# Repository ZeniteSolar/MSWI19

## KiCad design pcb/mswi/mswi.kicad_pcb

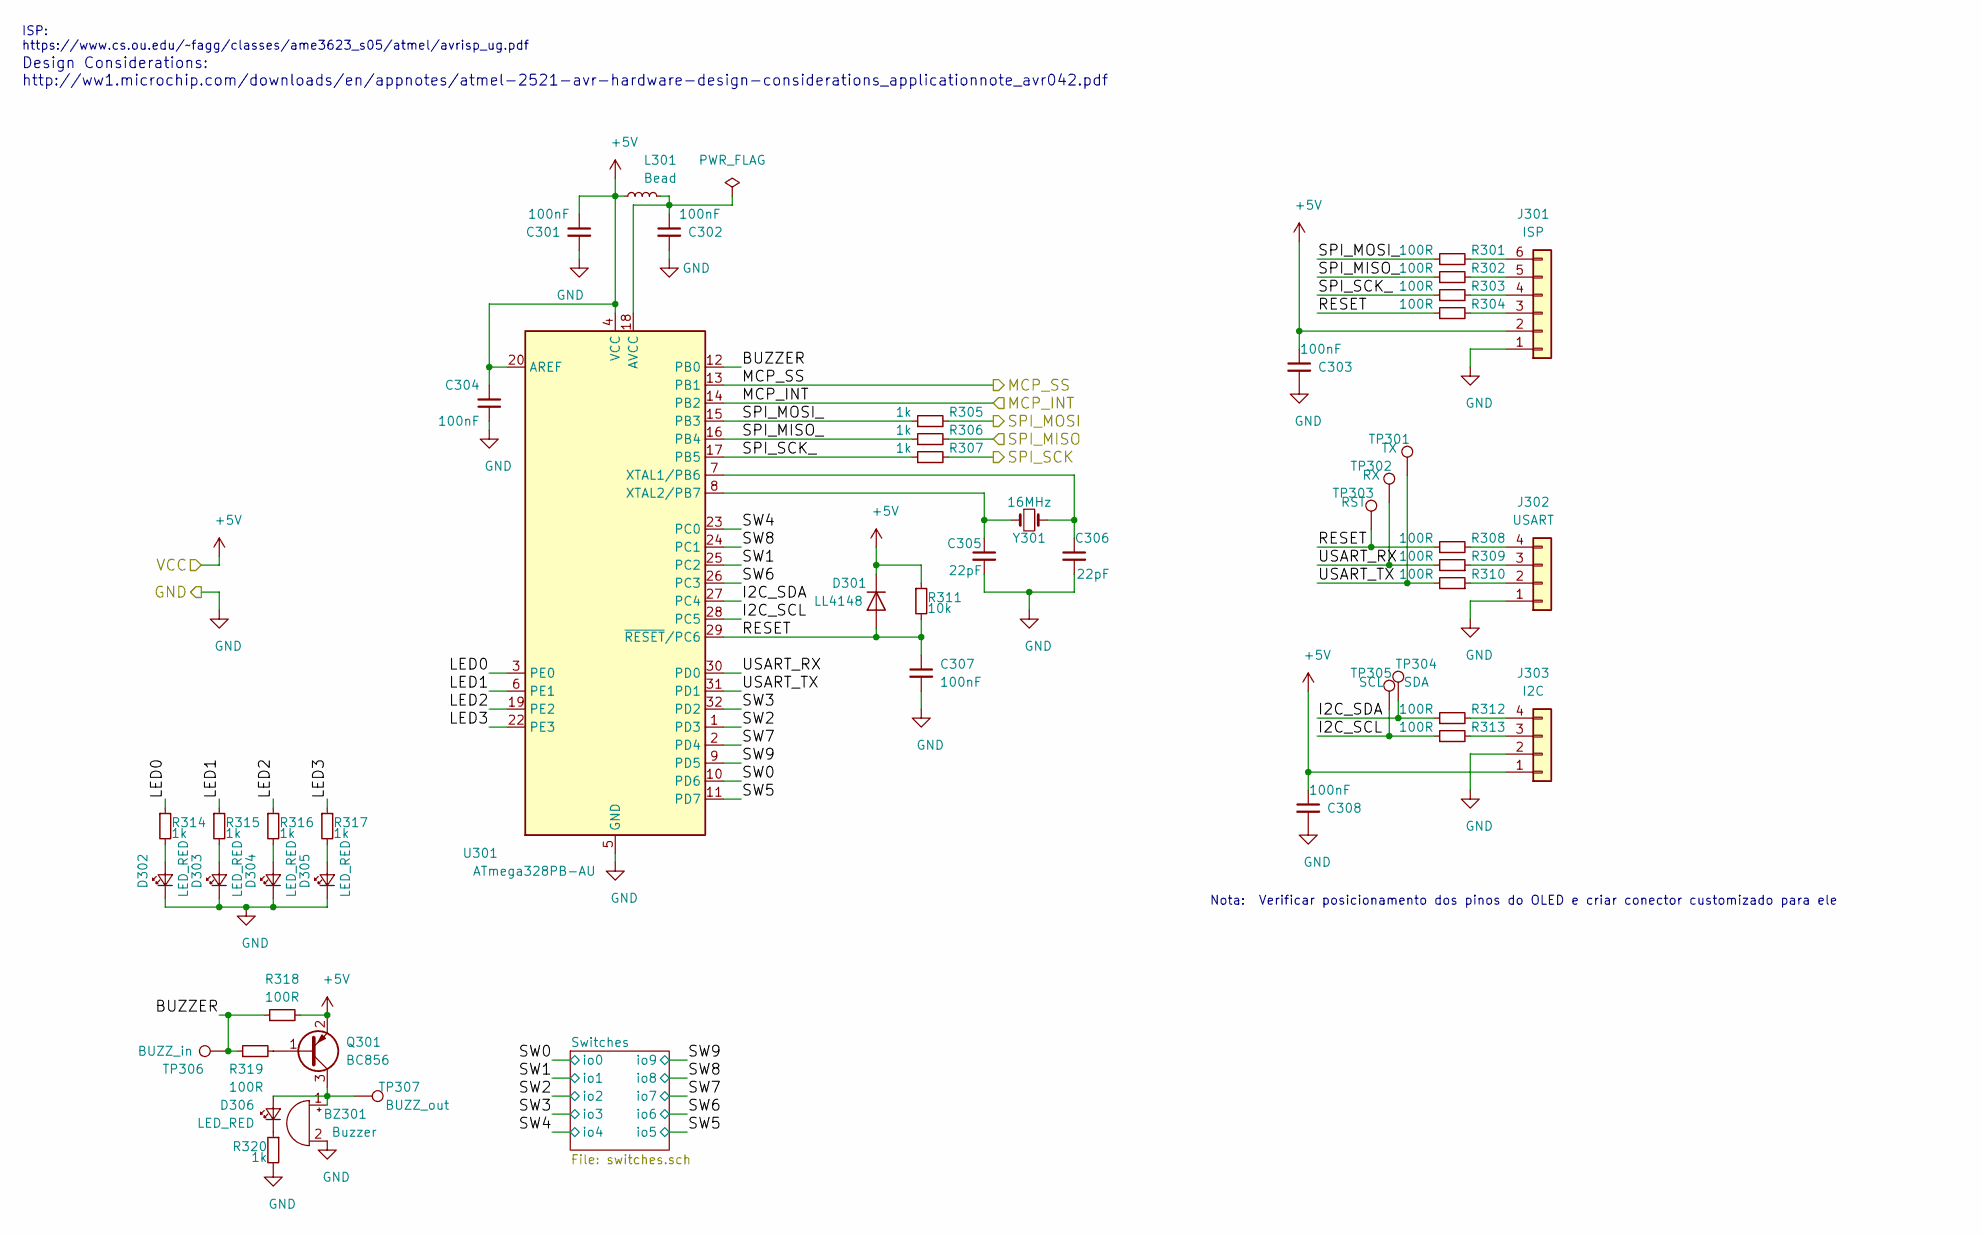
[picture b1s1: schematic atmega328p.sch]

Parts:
BZ301: Buzzer; Buzzer_12x9.5RM7.6
C301, C302, C303, C304, C307, C308: 100nF; C_0805_2012Metric_Pad1.15x1.40mm_HandSolder
C305, C306: 22pF; C_0805_2012Metric_Pad1.15x1.40mm_HandSolder
D301: LL4148; D_MiniMELF_Handsoldering
D302, D303, D304, D305, D306: LED_RED; LED_0805_2012Metric_Pad1.15x1.40mm_HandSolder
J301: ISP; PinHeader_1x06_P2.54mm_Vertical
J302: USART; PinHeader_1x04_P2.54mm_Vertical
J303: I2C; PinHeader_1x04_P2.54mm_Vertical
L301: Bead; L_0805_2012Metric_Pad1.15x1.40mm_HandSolder
Q301: BC856; SOT-23
R301, R302, R303, R304, R308, R309, R310, R312, R313, R318, R319: 100R; R_0805_2012Metric_Pad1.15x1.40mm_HandSolder
R305, R306, R307, R314, R315, R316, R317, R320: 1k; R_0805_2012Metric_Pad1.15x1.40mm_HandSolder
R311: 10k; R_0805_2012Metric_Pad1.15x1.40mm_HandSolder
TP301: TX; TestPoint_Pad_2.0x2.0mm
TP302: RX; TestPoint_Pad_2.0x2.0mm
TP303: RST; TestPoint_Pad_2.0x2.0mm
TP304: SDA; TestPoint_Pad_2.0x2.0mm
TP305: SCL; TestPoint_Pad_2.0x2.0mm
TP306: BUZZ_in; TestPoint_Pad_2.0x2.0mm
TP307: BUZZ_out; TestPoint_Pad_2.0x2.0mm
U301: ATmega328PB-AU; TQFP-32_7x7mm_P0.8mm
Y301: 16MHz; Crystal_HC49-U_Vertical

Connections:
+5V: C301.1, C303.1, C304.2, C308.1, D301.1 (K), J301.2, J303.1, L301.1, Q301.2 (E), R311.1, R318.2, U301.4 (VCC), U301.20 (AREF); also elsewhere on the board
/CANBUS/CS: U301.13 (PB1); also elsewhere on the board
/CANBUS/INT: U301.14 (PB2); also elsewhere on the board
/CANBUS/SCK: R307.2; also elsewhere on the board
/CANBUS/SI: R305.2; also elsewhere on the board
/CANBUS/SO: R306.2; also elsewhere on the board
/MCU/BUZZER: R318.1, R319.1, TP306.1, U301.12 (PB0)
/MCU/I2C_SCL: R313.1, TP305.1, U301.28 (PC5)
/MCU/I2C_SDA: R312.1, TP304.1, U301.27 (PC4)
/MCU/LED0: R314.1, U301.3 (PE0)
/MCU/LED1: R315.1, U301.6 (PE1)
/MCU/LED2: R316.1, U301.19 (PE2)
/MCU/LED3: R317.1, U301.22 (PE3)
/MCU/RESET: C307.1, D301.2 (A), R304.1, R308.1, R311.2, TP303.1, U301.29 (~RESET~/PC6)
/MCU/SPI_MISO_: R302.1, R306.1, U301.16 (PB4)
/MCU/SPI_MOSI_: R301.1, R305.1, U301.15 (PB3)
/MCU/SPI_SCK_: R303.1, R307.1, U301.17 (PB5)
/MCU/SW0: U301.10 (PD6); also elsewhere on the board
/MCU/SW1: U301.25 (PC2); also elsewhere on the board
/MCU/SW2: U301.1 (PD3); also elsewhere on the board
/MCU/SW3: U301.32 (PD2); also elsewhere on the board
/MCU/SW4: U301.23 (PC0); also elsewhere on the board
/MCU/SW5: U301.11 (PD7); also elsewhere on the board
/MCU/SW6: U301.26 (PC3); also elsewhere on the board
/MCU/SW7: U301.2 (PD4); also elsewhere on the board
/MCU/SW8: U301.24 (PC1); also elsewhere on the board
/MCU/SW9: U301.9 (PD5); also elsewhere on the board
/MCU/USART_RX: R309.2, TP302.1, U301.30 (PD0)
/MCU/USART_TX: R310.2, TP301.1, U301.31 (PD1)
GND: BZ301.2 (+), C301.2, C302.2, C303.2, C304.1, C305.2, C306.2, C307.2, C308.2, D302.1 (K), D303.1 (K), D304.1 (K), D305.1 (K), J301.1, J302.1, J303.2, R320.2, U301.5 (GND), U301.21 (GND); also elsewhere on the board
unnamed: BZ301.1 (-), D306.2 (A), Q301.3 (C), TP307.1
unnamed: C302.1, L301.2, U301.18 (AVCC)
unnamed: C305.1, U301.8 (XTAL2/PB7), Y301.1
unnamed: C306.1, U301.7 (XTAL1/PB6), Y301.2
unnamed: D302.2 (A), R314.2
unnamed: D303.2 (A), R315.2
unnamed: D304.2 (A), R316.2
unnamed: D305.2 (A), R317.2
unnamed: D306.1 (K), R320.1
unnamed: J301.3, R304.2
unnamed: J301.4, R303.2
unnamed: J301.5, R302.2
unnamed: J301.6, R301.2
unnamed: J302.2, R310.1
unnamed: J302.3, R309.1
unnamed: J302.4, R308.2
unnamed: J303.3, R313.2
unnamed: J303.4, R312.2
unnamed: Q301.1 (B), R319.2

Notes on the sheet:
Design Considerations: http://ww1.microchip.com/downloads/en/appnotes/atmel-2521-avr-hardware-design-considerations_applicationnote_avr042.pdf
ISP: https://www.cs.ou.edu/~~fagg/classes/ame3623_s05/atmel/avrisp_ug.pdf
Nota: Verificar posicionamento dos pinos do OLED e criar conector customizado para ele

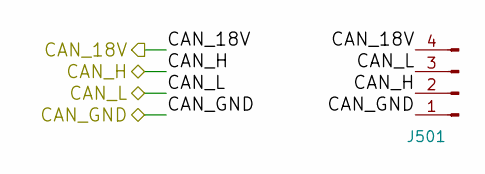
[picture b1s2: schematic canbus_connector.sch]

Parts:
J501: Conn_01x04_Male

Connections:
/CANBUS CONN/CAN_GND: J501.1; also elsewhere on the board
/CANBUS CONN/CAN_H: J501.2; also elsewhere on the board
/CANBUS CONN/CAN_L: J501.3; also elsewhere on the board
/POWER SUPPLY/+18V_IN: J501.4; also elsewhere on the board

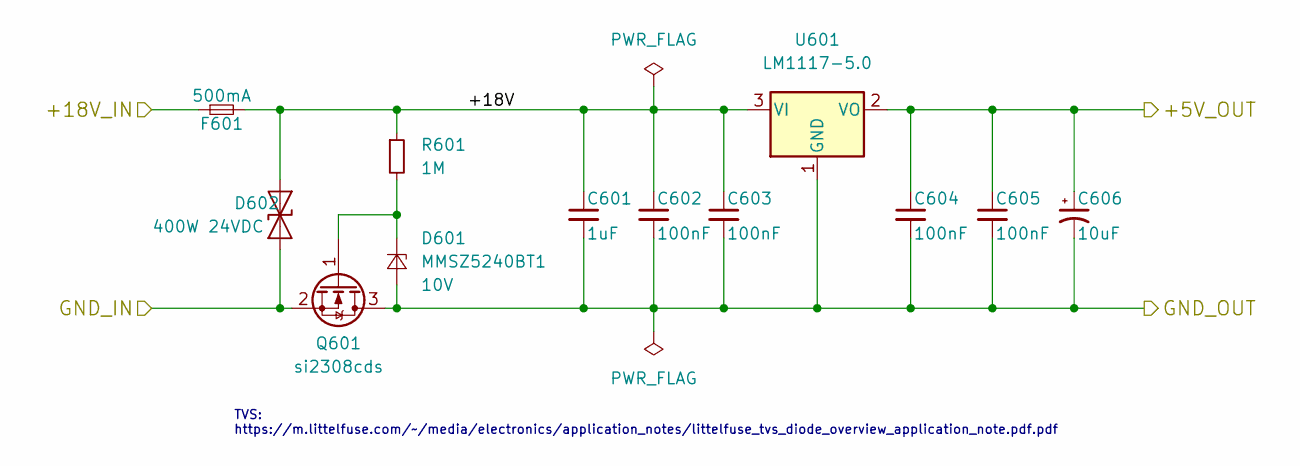
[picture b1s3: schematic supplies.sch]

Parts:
C601: 1uF; C_0805_2012Metric_Pad1.15x1.40mm_HandSolder
C602, C603, C604, C605: 100nF; C_0805_2012Metric_Pad1.15x1.40mm_HandSolder
C606: 10uF; CP_EIA-6032-20_AVX-F_Pad2.25x2.35mm_HandSolder
D601: MMSZ5240BT1; D_SOD-123; Voltage 10V
D602: 400W 24VDC; D_SMA
F601: 500mA; Fuse_1206_3216Metric_Pad1.42x1.75mm_HandSolder
Q601: si2308cds; SOT-23
R601: 1M; R_0805_2012Metric_Pad1.15x1.40mm_HandSolder
U601: LM1117-5.0; SOT-223-3_TabPin2

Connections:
+5V: C604.1, C605.1, C606.1, U601.2 (VO); also elsewhere on the board
/CANBUS CONN/CAN_GND: D602.2 (A2), Q601.2 (S); also elsewhere on the board
/POWER SUPPLY/+18V: C601.1, C602.1, C603.1, D602.1 (A1), F601.2, R601.1, U601.3 (VI)
/POWER SUPPLY/+18V_IN: F601.1; also elsewhere on the board
GND: C601.2, C602.2, C603.2, C604.2, C605.2, C606.2, D601.2 (A), Q601.3 (D), U601.1 (GND); also elsewhere on the board
unnamed: D601.1 (K), Q601.1 (G), R601.2

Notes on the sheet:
TVS: https://m.littelfuse.com/~~/media/electronics/application_notes/littelfuse_tvs_diode_overview_application_note.pdf.pdf

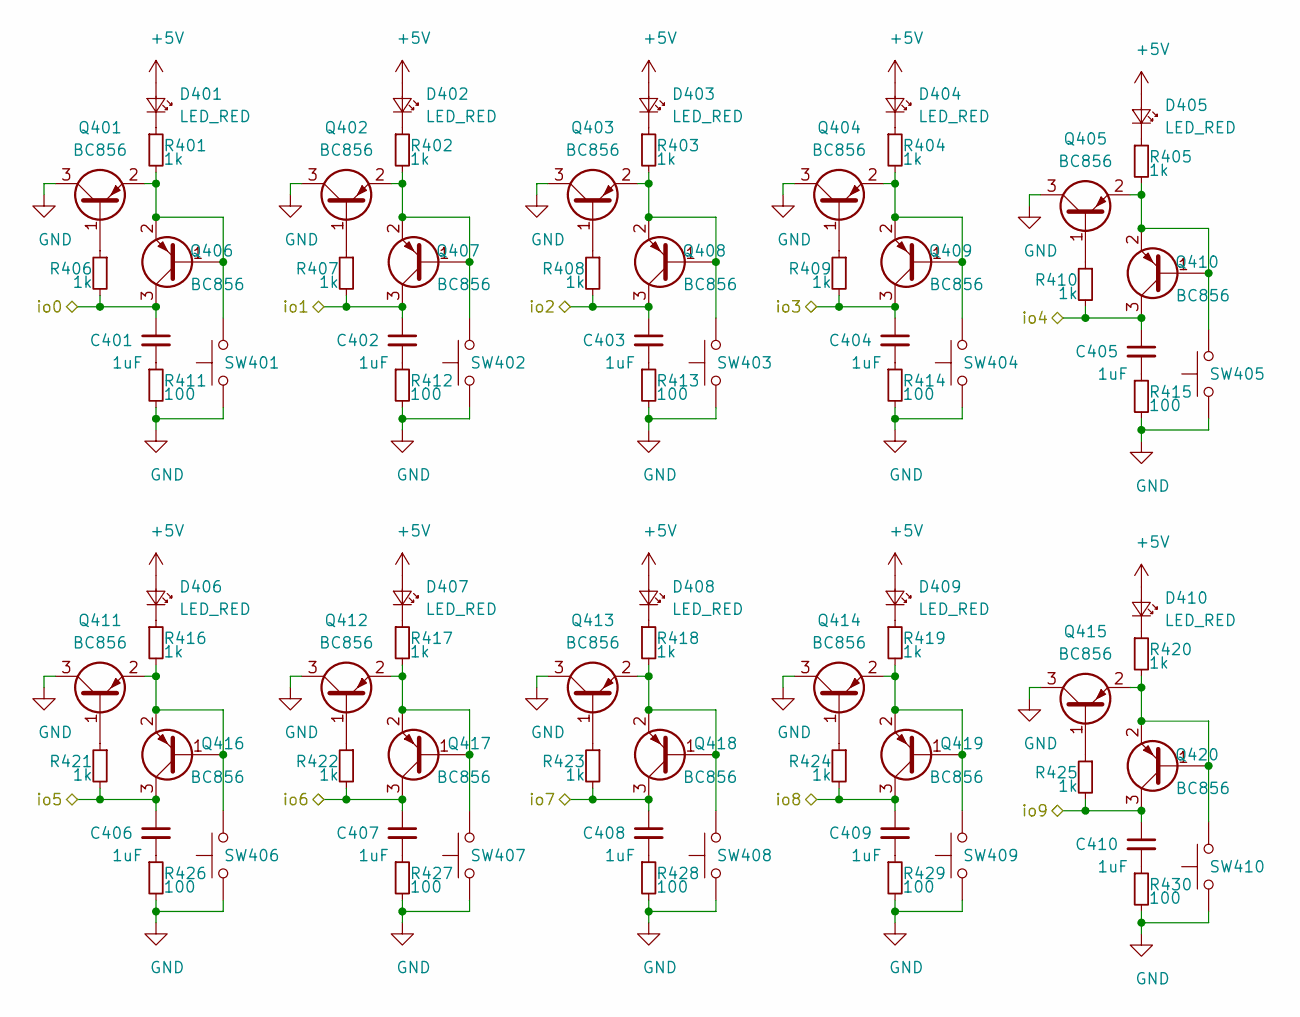
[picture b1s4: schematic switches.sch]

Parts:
C401, C402, C403, C404, C405, C406, C407, C408, C409, C410: 1uF; C_0805_2012Metric_Pad1.15x1.40mm_HandSolder
D401, D402, D403, D404, D405, D406, D407, D408, D409, D410: LED_RED; LED_0805_2012Metric_Pad1.15x1.40mm_HandSolder
Q401, Q402, Q403, Q404, Q405, Q406, Q407, Q408, Q409, Q410, Q411, Q412, Q413, Q414, Q415, Q416, Q417, Q418, Q419, Q420: BC856; SOT-23
R401, R402, R403, R404, R405, R406, R407, R408, R409, R410, R416, R417, R418, R419, R420, R421, R422, R423, R424, R425: 1k; R_0805_2012Metric_Pad1.15x1.40mm_HandSolder
R411, R412, R413, R414, R415, R426, R427, R428, R429, R430: 100; R_0805_2012Metric_Pad1.15x1.40mm_HandSolder
SW401, SW402, SW403, SW404, SW405, SW406, SW407, SW408, SW409, SW410: SW_Push; SW_PUSH-12mm

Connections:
+5V: D401.2 (A), D402.2 (A), D403.2 (A), D404.2 (A), D405.2 (A), D406.2 (A), D407.2 (A), D408.2 (A), D409.2 (A), D410.2 (A); also elsewhere on the board
/MCU/SW0: C401.1, Q406.3 (C), R406.2; also elsewhere on the board
/MCU/SW1: C402.1, Q407.3 (C), R407.2; also elsewhere on the board
/MCU/SW2: C403.1, Q408.3 (C), R408.2; also elsewhere on the board
/MCU/SW3: C404.1, Q409.3 (C), R409.2; also elsewhere on the board
/MCU/SW4: C405.1, Q410.3 (C), R410.2; also elsewhere on the board
/MCU/SW5: C406.1, Q416.3 (C), R421.2; also elsewhere on the board
/MCU/SW6: C407.1, Q417.3 (C), R422.2; also elsewhere on the board
/MCU/SW7: C408.1, Q418.3 (C), R423.2; also elsewhere on the board
/MCU/SW8: C409.1, Q419.3 (C), R424.2; also elsewhere on the board
/MCU/SW9: C410.1, Q420.3 (C), R425.2; also elsewhere on the board
GND: Q401.3 (C), Q402.3 (C), Q403.3 (C), Q404.3 (C), Q405.3 (C), Q411.3 (C), Q412.3 (C), Q413.3 (C), Q414.3 (C), Q415.3 (C), R411.2, R412.2, R413.2, R414.2, R415.2, R426.2, R427.2, R428.2, R429.2, R430.2, SW401.1, SW402.1, SW403.1, SW404.1, SW405.1, SW406.1, SW407.1, SW408.1, SW409.1, SW410.1; also elsewhere on the board
unnamed: C401.2, R411.1
unnamed: C402.2, R412.1
unnamed: C403.2, R413.1
unnamed: C404.2, R414.1
unnamed: C405.2, R415.1
unnamed: C406.2, R426.1
unnamed: C407.2, R427.1
unnamed: C408.2, R428.1
unnamed: C409.2, R429.1
unnamed: C410.2, R430.1
unnamed: D401.1 (K), R401.1
unnamed: D402.1 (K), R402.1
unnamed: D403.1 (K), R403.1
unnamed: D404.1 (K), R404.1
unnamed: D405.1 (K), R405.1
unnamed: D406.1 (K), R416.1
unnamed: D407.1 (K), R417.1
unnamed: D408.1 (K), R418.1
unnamed: D409.1 (K), R419.1
unnamed: D410.1 (K), R420.1
unnamed: Q401.1 (B), R406.1
unnamed: Q401.2 (E), Q406.1 (B), Q406.2 (E), R401.2, SW401.2
unnamed: Q402.1 (B), R407.1
unnamed: Q402.2 (E), Q407.1 (B), Q407.2 (E), R402.2, SW402.2
unnamed: Q403.1 (B), R408.1
unnamed: Q403.2 (E), Q408.1 (B), Q408.2 (E), R403.2, SW403.2
unnamed: Q404.1 (B), R409.1
unnamed: Q404.2 (E), Q409.1 (B), Q409.2 (E), R404.2, SW404.2
unnamed: Q405.1 (B), R410.1
unnamed: Q405.2 (E), Q410.1 (B), Q410.2 (E), R405.2, SW405.2
unnamed: Q411.1 (B), R421.1
unnamed: Q411.2 (E), Q416.1 (B), Q416.2 (E), R416.2, SW406.2
unnamed: Q412.1 (B), R422.1
unnamed: Q412.2 (E), Q417.1 (B), Q417.2 (E), R417.2, SW407.2
unnamed: Q413.1 (B), R423.1
unnamed: Q413.2 (E), Q418.1 (B), Q418.2 (E), R418.2, SW408.2
unnamed: Q414.1 (B), R424.1
unnamed: Q414.2 (E), Q419.1 (B), Q419.2 (E), R419.2, SW409.2
unnamed: Q415.1 (B), R425.1
unnamed: Q415.2 (E), Q420.1 (B), Q420.2 (E), R420.2, SW410.2

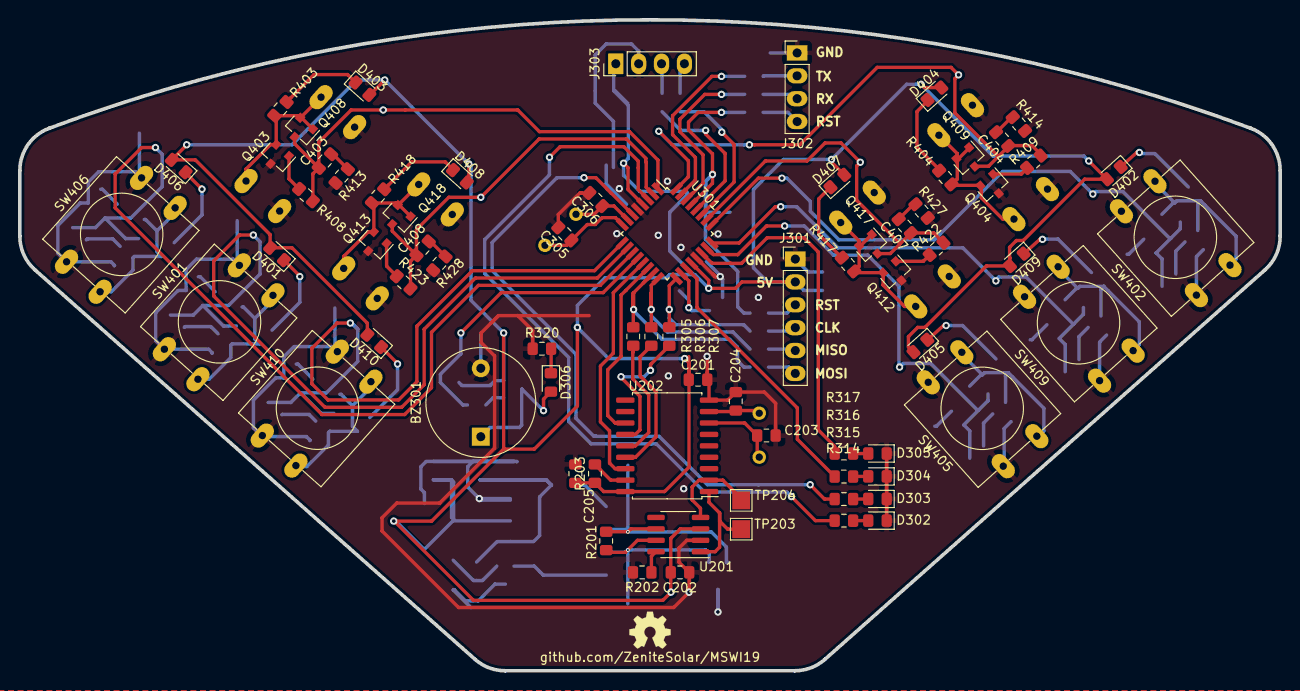
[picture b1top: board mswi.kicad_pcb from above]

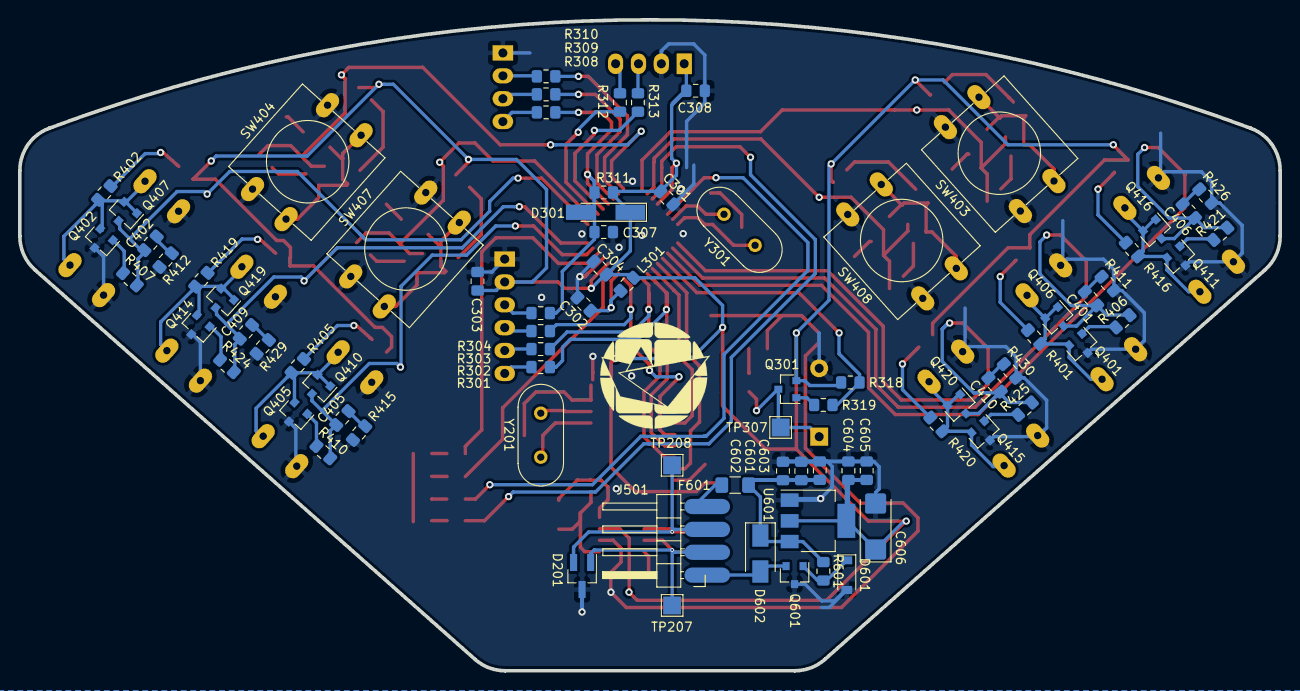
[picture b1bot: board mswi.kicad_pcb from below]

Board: 2 copper layers, 140.0 x 72.3 mm, 152 parts (80 on the bottom side), 101 nets.

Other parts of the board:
C201, C202, C205: 100nF; C_0805_2012Metric_Pad1.15x1.40mm_HandSolder
C203, C204: 22pF; C_0805_2012Metric_Pad1.15x1.40mm_HandSolder
D201: pesd1can; SOT-23_Handsoldering
R201: 120; R_0805_2012Metric_Pad1.15x1.40mm_HandSolder
R202: 4k7; R_0805_2012Metric_Pad1.15x1.40mm_HandSolder
R203: 10k; R_0805_2012Metric_Pad1.15x1.40mm_HandSolder
TP203: TXCAN; TestPoint_Pad_2.0x2.0mm
TP204: RXCAN; TestPoint_Pad_2.0x2.0mm
TP207: CAN_H; TestPoint_Pad_2.0x2.0mm
TP208: CAN_L; TestPoint_Pad_2.0x2.0mm
U201: MCP2551-I/SN; SOIC-8_3.9x4.9mm_P1.27mm
U202: MCP2515-xSO; SOIC-18W_7.5x11.6mm_P1.27mm
Y201: 16MHz; Crystal_HC49-U_Vertical

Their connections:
+5V: C201.1, C202.1, C205.1, R203.1, U201.3, U202.18; also elsewhere on the board
/CANBUS CONN/CAN_H: D201.1, R201.2, TP207.1, U201.7; also elsewhere on the board
/CANBUS CONN/CAN_L: D201.2, R201.1, TP208.1, U201.6; also elsewhere on the board
/CANBUS/CS: U202.16; also elsewhere on the board
/CANBUS/INT: U202.12; also elsewhere on the board
/CANBUS/RXCAN: TP204.1, U201.4, U202.2
/CANBUS/SCK: U202.13; also elsewhere on the board
/CANBUS/SI: U202.14; also elsewhere on the board
/CANBUS/SO: U202.15; also elsewhere on the board
/CANBUS/TXCAN: TP203.1, U201.1, U202.1
GND: C201.2, C202.2, C203.2, C204.2, C205.2, D201.3, R202.2, U201.2, U202.9; also elsewhere on the board
unnamed: C203.1, U202.7, Y201.1
unnamed: C204.1, U202.8, Y201.2
unnamed: R202.1, U201.8
unnamed: R203.2, U202.17

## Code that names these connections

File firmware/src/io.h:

/**
 * @file io.h
 *
 * @defgroup IO IO Module
 *
 * @brief Specific module for buzzer, leds and switches interfaces.
 *
 */

#ifndef IO_H
#define IO_H
           
#include <avr/io.h>
#include <stdlib.h>
#include "../lib/bit_utils.h"
#include "conf.h"
#include <util/delay.h>
#include "dbg_vrb.h"
#include "usart.h"

typedef enum { direction_input, direction_output } direction_t;
typedef enum { pullup_disabled, pullup_enabled } pullup_t;
typedef enum { switch_pressed, switch_released } switch_status_t;

typedef union{
    struct{
        uint16_t sw4    :1,  // PC0
                 sw8    :1,  // PC1
                 sw1    :1,  // PC2
                 sw6    :1,  // PC3
                        :1,  // PC4
                        :1,  // PC5
                        :1,  // PC6
                        :1,  // PC7
                        :1,  // PD0
                        :1,  // PD1
                 sw3    :1,  // PD2
                 sw2    :1,  // PD3
                 sw7    :1,  // PD4
                 sw9    :1,  // PD5
                 sw0    :1,  // PD6
                 sw5    :1;  // PD7
    };
    struct{
        uint16_t high   :8,  // C
                 low    :8;  // D
    };
    uint16_t all;
} switches_t;

#define SW_PIN 	(((PIND) << 8) | (PINC))
#define SW_PORT	(((PORTD) << 8) | (PORTC))
#define SW_DDR 	(((DDRD) << 8) | (DDRC))

extern switches_t switches;

typedef union{
    struct{
        uint8_t led0    :1,  // PE0
                led1    :1,  // PE1
                led2    :1,  // PE2
                led3    :1,  // PE3
                        :4;  // others
    };
    uint8_t all;
} leds_t;

typedef enum { led_off, led_on } led_state_t;

#define leds    	(*(volatile leds_t *)&PORTE)
#define LEDS_DDR 	(DDRE)

typedef union{
    struct{
        uint8_t buzzer0 :1,   // PB0
                        :7;   // others
    };
    uint8_t all;
} buzzer_t;

typedef enum { buzzer_on, buzzer_off } buzzer_state_t;
typedef enum { 
    buzzer_beep0 = 0,
    buzzer_beep1 = 1,
    buzzer_beep2 = 10,
    buzzer_beep3 = 25,
    buzzer_beep4 = 50,
    buzzer_beep5 = 100,
    buzzer_beep6 = 200,
} buzzer_beep_t;

#define buzzer    	(*(volatile buzzer_t *)&PORTB)
#define BUZZER_DDR  (DDRB)

void leds_init(void);
void switches_init(void);
void buzzer_init(void);

void switches_read(void);
void switches_direction(direction_t direction);

void buzzer_beep(uint16_t ms);

#endif

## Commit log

2019-08-27 Ignoring refs folder
2019-08-30 initial design
2019-08-30 initial design loaded into kicad
2019-09-04 Oportunidades, prospecção, levantamento de dados
2019-09-04 Reorganizado
2019-09-04 images for the first design iteration
2019-09-04 primeira iteração no design
2019-09-04 names fixed
2019-10-02 resultado do mudge sobre os itens no volante
2019-10-10 ignoring unneeded kicad files
2019-10-10 Full schematic added. (To be revised).
2019-10-11 ignoring simulation logs and outputs
2019-10-11 all done
2019-10-11 switches reworked, buzzer added
2019-10-11 Schematics Annotated
2019-10-11 Footprints associated
2019-10-11 Test points added. Buzz footprint added
2019-10-11 Schematic PDF added
2019-10-11 renamed to avoid problems with KiCAD
2019-10-11 components imported
2019-10-11 TODO list added
2019-10-11 TODO list updated
2019-10-11 PCB geometry added
2019-10-11 ISP connector changed to vertical
2019-10-11 Switch&led interface first iteration
2019-10-11 Buzzer interface first iteration
2019-10-11 all swiches&leds interface routed
2019-10-11 TVS added
2019-10-11 input and power supply routed
2019-10-11 PDF updated
2019-10-11 CANBUS connector changed
2019-10-11 CANBUS connector changed, footprint added
2019-10-11 pwr sup. rounted with new can connector
2019-10-11 screws removed
2019-10-11 working...
2019-10-11 routing: wip
2019-10-16 Routing done. Needs rework to fabrication
2019-10-16 Rules adapted to the manufactoring method (CNC)
2019-10-16 SW 3D added
2019-10-16 Silkscreen organized
2019-10-16 Fab annotations done
2019-10-16 leds changed to front
2019-10-16 buzzer and switch 3D enhanced
2019-10-22 Done. Adjusted for standart industrial capability
2019-10-22 Simple alternative for input power supply
2019-10-22 Models ok
2019-10-22 3D mdoels updated
2019-10-22 3D exported
2019-10-23 3d render and .pretty lib
2019-10-24 CAN H and L wasnt properly connected
2019-11-06 implementaçção documentada
2019-11-06 pequenos ajustes para produção
2019-11-06 ajuste na formatação
2019-11-21 gitignore added
2019-11-21 hello world
2019-11-27 borrowed from MVC19
2019-11-28 Working hello world with display.
    - Makefiles updated to compile for atmega328pb.
    - Firmware was cleaned,
    - Working display with a "Hello World!" message.
    - Usart working
    - Leds addressed but not tested yet!
    - CAN not working yet!
2019-11-28 CAN initialized. Need to be tested with others CAN devices.
2019-12-01 DISPLAYS library cleaned
2019-12-01 makefiles updated
2019-12-08 exploring a difference approach for IO interfaces
2019-12-08 binary for 16bits added
2019-12-08 initial 3D design to be printed
2019-12-08 an initial chronometer implemented
2019-12-08 edge macros added
2019-12-08 input module implemented
2019-12-08 added all inputs
2019-12-08 callbacks working
2019-12-08 calling unknown callback fixed
2019-12-09 cleaned
2019-12-09 i2c frequency upgraded to 800kHz
2019-12-10 serial connection added after upload
2019-12-11 hex generation fixed
2019-12-14 chronometer showing formatted time
2019-12-14 frequency computation fixed
2019-12-14 prescaler adjusted to minimize errors
2019-12-14 inline removed
2019-12-14 ui design updated
2019-12-14 screen change implemented
2019-12-14 build ignored
2019-12-15 power controller implemented
2019-12-15 beeps added
2020-01-18 teste de comunicação com o MAM
2020-01-20 avr-can-lib updated
2020-01-20 adjusted to compile for atmega328pb
2020-01-20 can_ids removed, makelibs updated
2020-01-20 updating MAB CAN messages
2020-01-20 updating MIC CAN messages
2020-01-21 updating MAM and GENERIC CAN messages
2020-01-21 compiling but need to be tested
2020-01-21 makelibs updated
2020-01-25 macros update
2020-01-25 using software spi
2020-01-25 D range adjusted for MIC
2020-02-14 .gitignore updated
2021-04-27 undef LEN and PREC
2022-05-09 fix multiple definition for new versions of gcc
2022-05-09 docs for how to burn bootloader and compile
2022-06-27 Add BOM
